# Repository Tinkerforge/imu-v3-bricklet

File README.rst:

IMU Bricklet 3.0
================

This repository contains the firmware source code and the hardware design
files. The documentation generator configs can be found at
https://github.com/Tinkerforge/generators

Repository Content
------------------

software/:
 * examples/: Examples for all supported languages
 * build/: Compiled files
 * src/: Source code of firmware
 * Makefile: Makefile to build project

hardware/:
 * Contains KiCad project files and additionally schematics as PDF

datasheets/:
 * Contains datasheets for sensors and complex ICs that are used

Hardware
--------

The hardware is designed with the open source EDA Suite KiCad
(http://www.kicad.org). Before you are able to open the files,
you have to install the Tinkerforge kicad-libraries
(https://github.com/Tinkerforge/kicad-libraries). You can either clone
them directly in hardware/ or clone them in a separate folder and
symlink them into hardware/
(ln -s kicad_path/kicad-libraries project_path/hardware). After that you
can open the .pro file in hardware/ with KiCad and from there view and
modify the schematics and the PCB layout.

Software
--------

If you want to do your own Brick/Bricklet firmware development we highly
recommend that you use our build environment setup script and read the
tutorial (https://www.tinkerforge.com/en/doc/Tutorials/Tutorial_Build_Environment/Tutorial.html).

To compile the C code we recommend you to install the newest GNU Arm Embedded
Toolchain (https://launchpad.net/gcc-arm-embedded/+download).
You also need to install bricklib2 (https://github.com/Tinkerforge/bricklib2).

You can either clone it directly in software/src/ or clone it in a
separate folder and symlink it into software/src/
(ln -s bricklib_path/bricklib2 project_path/software/src/). Finally make sure to
have CMake installed (http://www.cmake.org/cmake/resources/software.html).

After that you can build the firmware by invoking make in software/.
The firmware (.zbin) can then be found in software/build/ and uploaded
with brickv (click button "Flashing" on start screen).

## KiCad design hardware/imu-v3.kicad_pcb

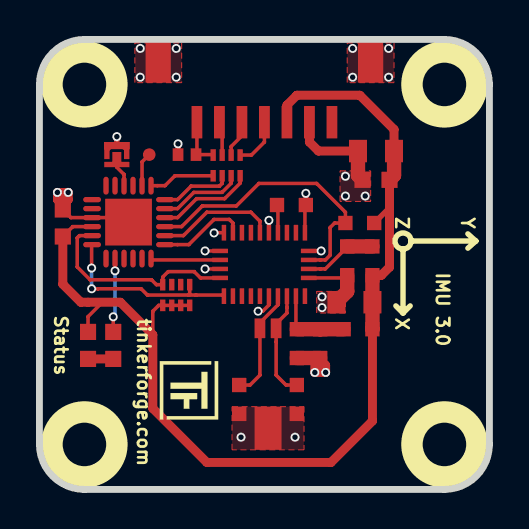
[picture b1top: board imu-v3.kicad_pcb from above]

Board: 2 copper layers, 25.0 x 25.0 mm, 30 parts (2 on the bottom side), 25 nets.

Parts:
C1: 220pF; C0402F
C2: 10uF; C0805
C3: 1uF; C0603F
C4, C5: 22pF; C0603
C6: 100nF; C0603F
C7, C8: 100nF; C0603
C9: 6.8nF; C0603
C10: 120nF; C0603
C11: 4.7µF; C0805
D1: blue; D0603F
L1, L2: INDUCTOR; C0603
P1: CON-SENSOR2
P2: BOOT; SolderJumper
P3: DEBUG; DEBUG_PAD
R1: 10k; R0603
R3: 1k; R0603F
RP1: 82; 4X0402
RP2: 3,9k; 4X0402
U1: XMC1302; QFN24-4x4mm-0.5mm
U2: BNO055; LGA28_5832
U3, U4, U5, U6: DRILL; DRILL_NP
VAL: WEEE_7mm
VAL#2: CE_5mm
X1: 32.768kHz; AB26TRQ

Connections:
BNO-ADR-SELECT: U1.18, U2.17
BNO-BOOT: R1.2, U1.21, U2.4
BNO-I2C-SCL: RP2.4, U1.11, U2.19
BNO-I2C-SDA: RP2.1, U1.12, U2.20
BNO-INT: U1.19, U2.14
BNO-nRESET: U1.20, U2.11
GND: C1.2, C2.2, C3.2, C4.2, C5.2, C6.2, C7.2, C8.2, C9.2, C10.2, C11.2, P1.2, P1.EP, P2.1, U1.9, U1.EXP, U2.2, U2.5, U2.6, U2.10, U2.15, U2.16, U2.18, U2.25, X1.3
unnamed: C1.1, P1.7, RP1.4
unnamed: C4.1, U2.27, X1.1
unnamed: C5.1, U2.26, X1.2
unnamed: C7.1, U2.9
unnamed: C8.1, L2.2, U2.3
unnamed: C9.1, C10.1, L1.2, U2.28
unnamed: D1.2, R3.2
unnamed: P1.4, RP1.1
unnamed: P1.5, RP1.2
unnamed: P1.6, RP1.3
unnamed: P2.2, U1.4
unnamed: P3.1, U1.2
unnamed: R3.1, U1.14
S-CLK: RP1.7, U1.23
S-CS: RP1.8, U1.22
S-MISO: RP1.5, U1.1
S-MOSI: RP1.6, U1.24
VCC: C2.1, C3.1, C6.1, C11.1, D1.1, L1.1, L2.1, P1.3, R1.1, RP2.5, RP2.6, RP2.7, RP2.8, U1.10

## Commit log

2020-04-29 initial push
2020-04-30 first design
2020-04-30 ready for prototype
2020-04-30 changed silkscreen
2020-06-09 remove locked bno
2020-08-03 Add initial firmware stub
2020-08-03 specify processor as XMC1302
2020-08-05 Update datasheet
2020-08-05 Add implementation for get_all_data and save_calibration
2020-10-21 Add callback implementation
2020-10-26 Add examples
2020-10-28 add schematic
2020-10-28 add 3d data
2021-05-27 readme: Remove in-development marker
2021-05-27 Update changelog
2021-10-25 Update KiCad link
    https://www.kicad.org/blog/2021/10/Avoid-links-to-former-kicad-domain/
2022-04-19 examples: uc: Rename TF_HalContext to TF_HAL.
2022-04-27 uc: Adapt to bindings changes
2022-07-06 Add license files.
2023-03-09 Add LabVIEW examples
2024-05-22 In case of error during configuration, only try up to 5 times
    so we never can end up in an unnecessary endless loop
2024-05-22 Add ref for 2.0.1
2025-10-04 Fix compatibility with new Docker build image (GCC 14.2.1)
